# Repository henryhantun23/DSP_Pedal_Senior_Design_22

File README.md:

# DSP_Pedal_Senior_Design_22

ECE 49022 Team 2

David Nickel

Henry Oo

John Ramnthun

Michael Scirocco

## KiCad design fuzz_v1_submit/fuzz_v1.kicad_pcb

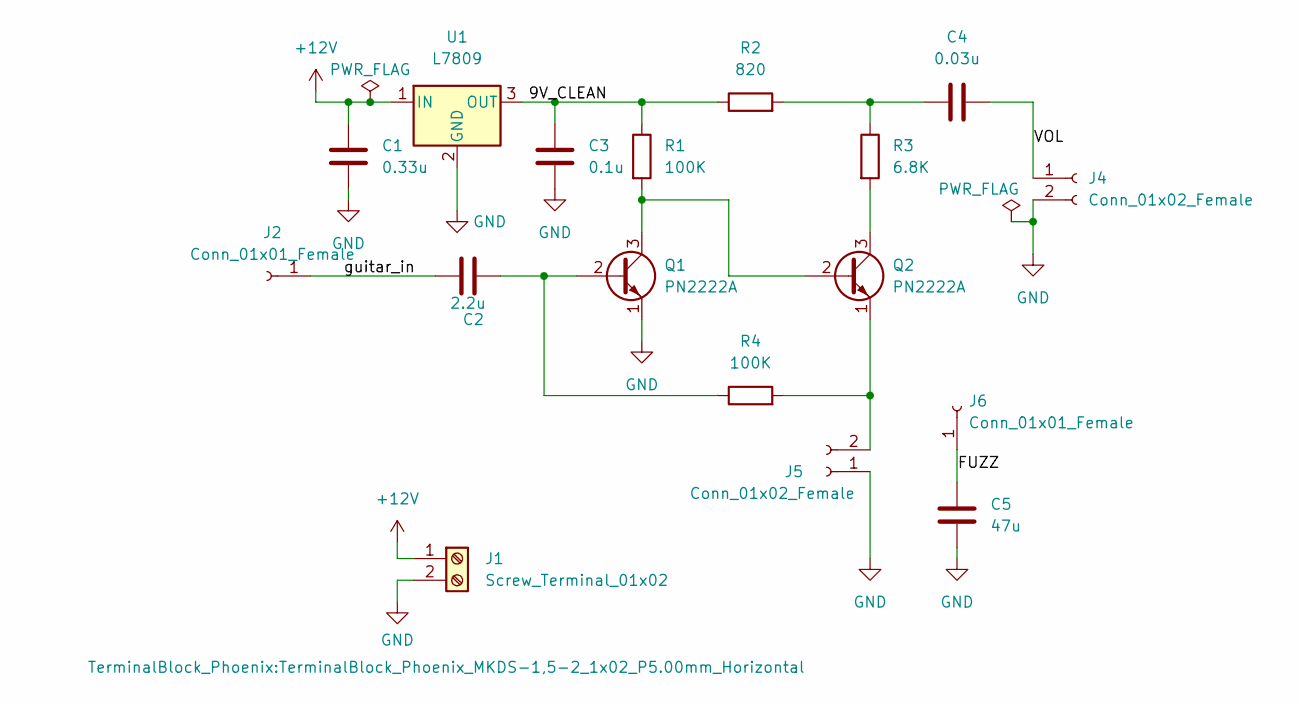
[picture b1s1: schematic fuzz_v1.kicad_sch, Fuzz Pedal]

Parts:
C1: 0.33u; C_0805_2012Metric_Pad1.18x1.45mm_HandSolder
C2: 2.2u; C_0805_2012Metric_Pad1.18x1.45mm_HandSolder
C3: 0.1u; C_0805_2012Metric_Pad1.18x1.45mm_HandSolder
C4: 0.03u; C_0805_2012Metric_Pad1.18x1.45mm_HandSolder
C5: 47u; C_0805_2012Metric_Pad1.18x1.45mm_HandSolder
J1: Screw_Terminal_01x02; TerminalBlock_Phoenix_MKDS-1,5-2_1x02_P5.00mm_Horizontal
J2, J6: Conn_01x01_Female; SolderWire-2.5sqmm_1x01_D2.4mm_OD4.4mm
J4, J5: Conn_01x02_Female; SolderWire-2.5sqmm_1x02_P7.2mm_D2.4mm_OD3.6mm
Q1, Q2: PN2222A; TO-92_Inline
R1, R4: 100K; R_0805_2012Metric_Pad1.20x1.40mm_HandSolder
R2: 820; R_0805_2012Metric_Pad1.20x1.40mm_HandSolder
R3: 6.8K; R_0805_2012Metric_Pad1.20x1.40mm_HandSolder
U1: L7809; TO-220-3_Vertical

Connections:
+12V: C1.1, J1.1, U1.1 (IN)
/9V_CLEAN: C3.1, R1.1, R2.1, U1.3 (OUT)
/FUZZ: C5.1, J6.1
/VOL: C4.2, J4.1
/guitar_in: C2.2, J2.1
GND: C1.2, C3.2, C5.2, J1.2, J4.2, J5.1, Q1.1 (E), U1.2 (GND)
unnamed: C2.1, Q1.2 (B), R4.1
unnamed: C4.1, R2.2, R3.1
unnamed: J5.2, Q2.1 (E), R4.2
unnamed: Q1.3 (C), Q2.2 (B), R1.2
unnamed: Q2.3 (C), R3.2

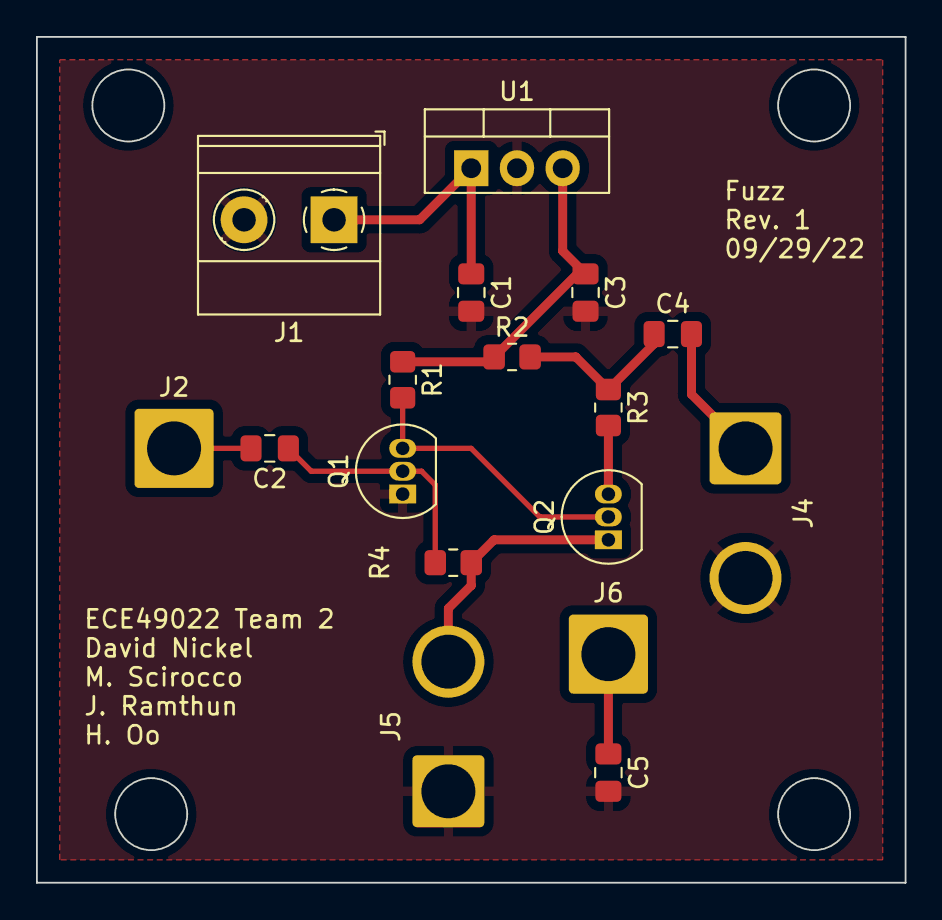
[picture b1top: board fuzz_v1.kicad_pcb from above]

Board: 2 copper layers, 48.3 x 47.0 mm, 17 parts (0 on the bottom side), 11 nets.

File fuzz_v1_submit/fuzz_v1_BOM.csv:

Comment,Designator,Footprint,LCSC Part Number
0.33u,C1,Capacitor_SMD:C_0805_2012Metric_Pad1.18x1.45mm_HandSolder,
2.2u,C2,Capacitor_SMD:C_0805_2012Metric_Pad1.18x1.45mm_HandSolder,
0.1u,C3,Capacitor_SMD:C_0805_2012Metric_Pad1.18x1.45mm_HandSolder,
0.03u,C4,Capacitor_SMD:C_0805_2012Metric_Pad1.18x1.45mm_HandSolder,
47u,C5,Capacitor_SMD:C_0805_2012Metric_Pad1.18x1.45mm_HandSolder,
Screw_Terminal_01x02,J1,"TerminalBlock_Phoenix:TerminalBlock_Phoenix_MKDS-1,5-2_1x02_P5.00mm_Horizontal",
Conn_01x01_Female,"J2,J6",Connector_Wire:SolderWire-2.5sqmm_1x01_D2.4mm_OD4.4mm,
Conn_01x02_Female,"J4,J5",Connector_Wire:SolderWire-2.5sqmm_1x02_P7.2mm_D2.4mm_OD3.6mm,
PN2222A,"Q1,Q2",Package_TO_SOT_THT:TO-92_Inline,
100K,"R1,R4",Resistor_SMD:R_0805_2012Metric_Pad1.20x1.40mm_HandSolder,
820,R2,Resistor_SMD:R_0805_2012Metric_Pad1.20x1.40mm_HandSolder,
6.8K,R3,Resistor_SMD:R_0805_2012Metric_Pad1.20x1.40mm_HandSolder,
L7809,U1,Package_TO_SOT_THT:TO-220-3_Vertical,

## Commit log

2022-10-16 ESP32 Looper Demo Code
    Files included are based on the ESP-IDF examples. Main file (looper_main.c) is used to currently: live translate audio from the ADC to the DAC, sample audio and record to flash, playback from flash. 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
2022-10-17 Looper circuit schematic
2022-10-17 Edited: Added Rubric docs and answered questions
2022-11-01 Final_fucking_looper_pcb_fingers_crossed
2022-11-22 Latest files to run looper
    Currently only supports 2 layers w/ no functionality after 2
2023-04-21 Upload demo code from Spark challenge
2023-04-21 Upload additional support docs
